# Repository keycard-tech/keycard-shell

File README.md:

# Keycard Shell

Keycard Shell transforms any Keycard into a standalone, air-gapped hardware wallet with built-in keypad, display, camera, and USB (which can be turned off). Fully open-source and EAL6+ certified, it uses ERC-4527 QR codes for secure signing and supports infinite removable backups.

## Main features

### Modular & Open Source

All firmware, hardware designs, and toolchain scripts are fully open source under the MIT license.

### Air-gapped Operation

Scan and display QR codes (ERC-4527) to sign transactions without ever exposing your keys.

### High-Security Secure Element

EAL6+ certified secure element for key storage and signing.

### Removable Smartcards

Support for an infinite number of Keycard smartcards, each with its own key & PIN.

### Wide Compatibility

Works seamlessly with MetaMask, imToken, Rabby, BlueWallet, Sparrow, Specter, and more.

### Built to Last

Powered by a replaceable Nokia BL-4C battery (25+ year expectancy), water & dust resistant.

### Duress PIN

A second PIN stops bad actors from stealing crypto by physical force

## About this repo

This repo contains everything needed to build a Keycard Shell.

### Repo structure

* `app`: the main firmware code. This is what makes everything happen.
* `bootloader`: the bootloader. Since it is non-upgradable we kept its complexity to a minimum.
* `cddl`: contains definitions for the various CBOR messages defined by the UR standard
* `deployment`: git-ignored folder containing the signing keys and build results
* `freertos`: we use FreeRTOS as our task scheduler.
* `hardware`: everything hardware related. From schematics up to case designs.
* `stm32`: all platform-specific code for the STM32H5 MCU. It also contains the project file for STM32CubeIDE needed to build the firmware.
* `test`: the tests firmware we run in the factory on each unit to check it has been properly assembled.
* `tools`: some tools used during the build process or during development.
* `zcbor`: the library we use to parse CBOR messages.

### Building the firmware

The Keycard Shell firmware build system uses CMake for the main firmware compilation and Python tools for post-processing (signing, image creation).

#### Getting the Code

First, clone the repository and switch to the release tag you want to build:

```bash
git clone https://github.com/keycard-tech/keycard-shell.git
cd keycard-shell
git checkout v1.1.1   # use the tag matching the official release you want to verify
```

make sure you follow the build instructions directly for the tag you checked out since some steps and toolchain versions can differ.

#### Prerequisites

##### Install Build Tools

**CMake** (3.15 or later) and **Ninja** are required for building the firmware.

On Ubuntu/Debian:
```bash
sudo apt install cmake ninja-build
```

On macOS (with Homebrew):
```bash
brew install cmake ninja
```

On Windows (with Chocolatey):
```bash
choco install cmake ninja
```

Alternatively, download from [cmake.org](https://cmake.org/download/) and [ninja-build.org](https://ninja-build.org/).

##### Install uv

```bash
curl -LsSf https://astral.sh/uv/install.sh | sh
```

or follow your OS instructions for installing uv.

##### Install ARM GCC Toolchain

Required for compiling STM32 firmware. The toolchain is automatically downloaded by the build script:

```bash
./tools/download-toolchain.sh
```

The script supports:
- Linux x86_64
- Linux aarch64
- macOS (Apple Silicon / arm64)
- Windows x86_64

After downloading, the toolchain is installed in `toolchain/`.

#### Setup Signing Keys

Create a `deployment` directory with two files:

- `bootloader-pubkey.txt`: Contains the public key the bootloader will use to verify the firmware. The key must be hex-encoded, uncompressed, and without the leading `04` byte.
- `fw-test-key.txt`: Contains a hex-encoded private key (the private part of the key in `bootloader-pubkey.txt`) used to sign the firmware.

#### Setup Virtual Environment

```bash
uv venv
uv sync
```

#### Build Firmware

```bash
cmake --preset release
cmake --build --preset release
```

#### Verifying the Firmware

After building, run:

```bash
uv run python tools/firmware-hash.py -b build/shellos.bin
```

Download the official binary from the [GitHub releases page](https://github.com/keycard-tech/keycard-shell/releases) and hash it the same way:

```bash
uv run python tools/firmware-hash.py -b ~/Downloads/shellos-<date>-<version>.bin
```

The two hashes must match.

#### Creating a Full Firmware Image

If you want to generate a full image to load on a device you built yourself, take a look at the `tools/create-image.py` script.

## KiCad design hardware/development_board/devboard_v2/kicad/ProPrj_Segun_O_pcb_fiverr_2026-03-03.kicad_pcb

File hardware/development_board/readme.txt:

For security reasons Shell in presales and sales have a locked bootloader that can only run firmwares which have been signed by Keycard CA key. This insures our users that they can trust the software they run. 

For developers who want to develop Shell firmware, you will find in this folder the full design of a development board for Shell

The folder '/devboard_v1' contains this design. Please note that there are some differences in the STM32 pinout between this development board version and shell board.

We'd need someone to update the layout of this dev board based on latest shell designs so that the dev board can actually run the shell builds.

Probably the best way to do this, would be to use the design and schematic from 'serial_run' version and make it in the form factor of this development board 

Get in touch with us either 
- on our discord server https://discord.gg/uJAXk7jFhZ
- our here with a GitHub issue or GitHub discussion

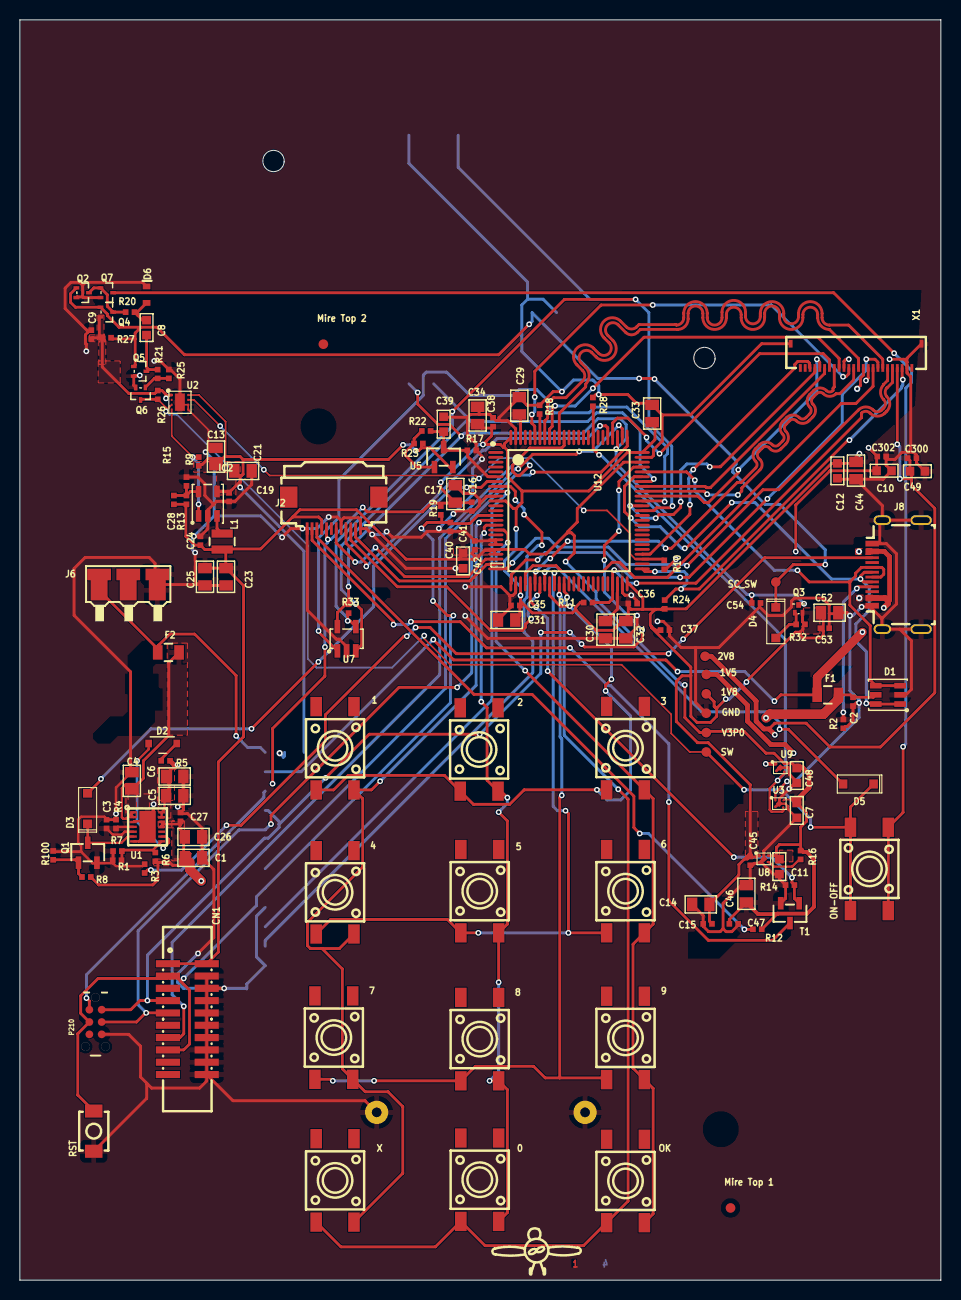
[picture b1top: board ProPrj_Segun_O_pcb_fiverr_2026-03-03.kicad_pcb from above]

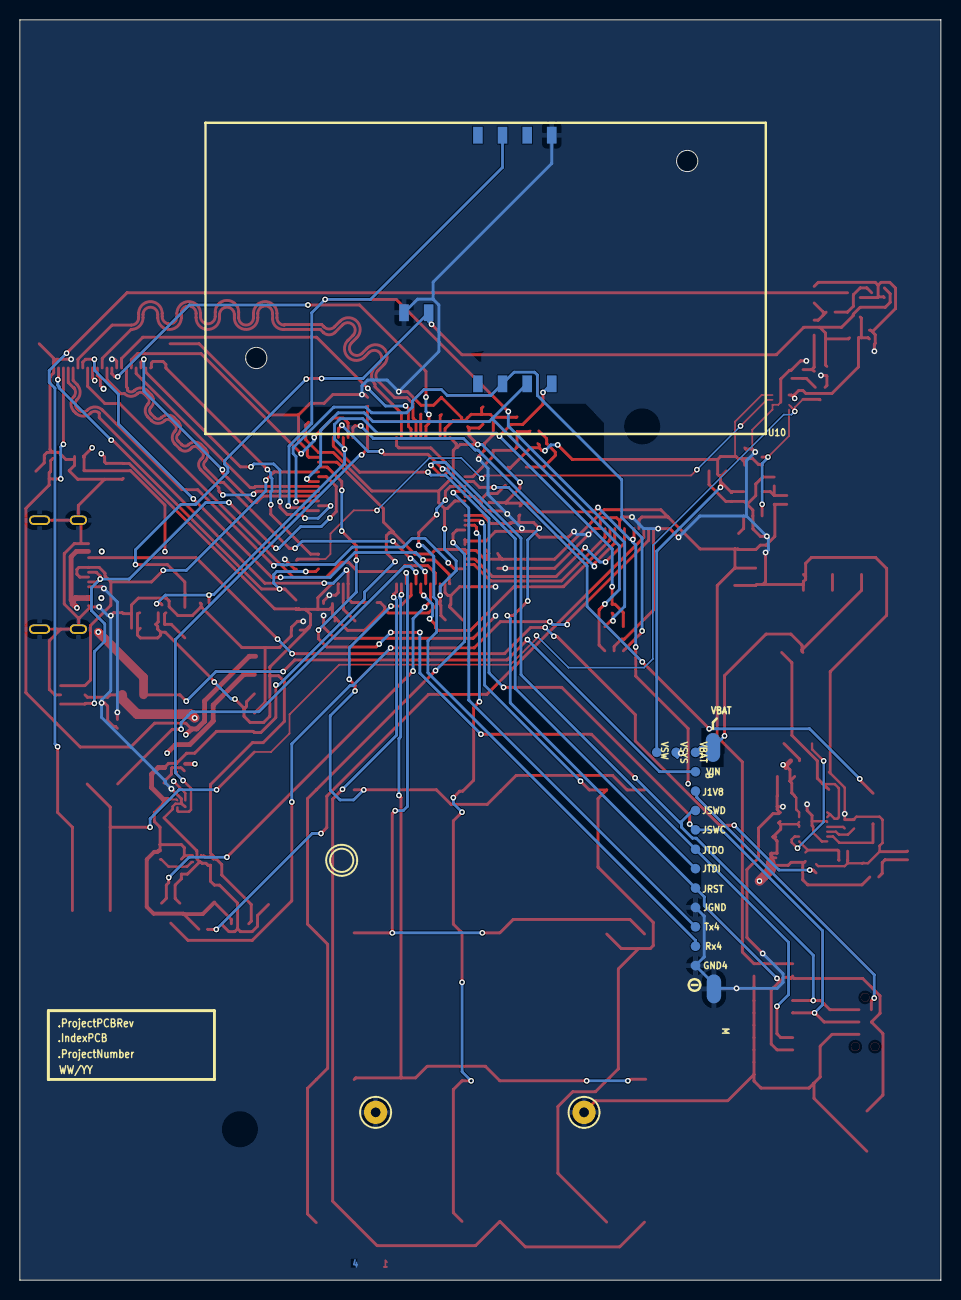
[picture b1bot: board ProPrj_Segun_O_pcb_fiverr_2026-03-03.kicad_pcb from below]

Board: 4 copper layers, 95.0 x 130.0 mm, 153 parts (17 on the bottom side), 85 nets.

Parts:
0, 1, 2, 3, 4, 5, 6, 7, 8, 9: KEY-SMD_4P-L6.0-W6.0-P3.90-LS9.0
1V5, 1V8, 2V8: TP; TESTPOINT_1MM
B: PLAGE_-_ROUGE
C1, C4, C5, C6, C13, C14, C17, C21, C23, C25, C26, C31, C32, C33, C34, C44, C46, C52: 4.7uF; 0805_-_CAPACITOR
C2, C9, C15, C16, C19, C24, C27, C35, C36, C37, C38, C40, C42, C45, C47, C53, C54, C300: 100nF; 0402_-_CAPACITOR
C3: 4.7uF; 0402_-_CAPACITOR
C7, C8, C10, C11, C12, C39, C41, C48: 1uF; 0603_-_CAPACITOR
C28: 9pF; 0402_-_CAPACITOR
C29, C30: 2.2uF; 0805_-_CAPACITOR
C49: 0603_-_CAPACITOR
C302: 0402_-_CAPACITOR
CN1: HX JN1.27-2x10 TP H4.9; CONN-SMD_HX-JN1.27-2X10-TP-H4.9
D1: 82400152; SOT23-6_0.95_VAR_AA
D2: LR_Y8SF-U1V2-1; OSRAM_LRY8SFU1V21
D3: MBR0530; SOD123_DIODE_INC
D4, D5: MBR0530T1G; SOD123_DIODE_INC
D6: BZX585-C3V0,115; SOD523_TOSHIBA
F1: BNP05000F000; 0805_-_FUSE
F2: 0ZCK0075FF2E; 0805_-_FUSE
GND: TESTPOINT_1MM
GND4: TP; TESTPOINT_1MM
IC2: SY8088IAAC; SOT23-5_0.95_VAR_AA
J1V8: TP; TESTPOINT_1MM
J2: FFC2B35-12-G; GCT_FFC2B35-12-G
J6: 1982633-1; TE_19826331
J8: U6252-35c; ANTENK_U6252-35C
JGND: TESTPOINT_1MM
JRST: TESTPOINT_1MM
JSWC: TESTPOINT_1MM
JSWD: TESTPOINT_1MM
JTDI: TESTPOINT_1MM
JTDO: TESTPOINT_1MM
L1: 2.2uH; CHILISON_BWF00252012
M: PLAGE_-_NOIRE
Mire Top 1, Mire Top 2: MIRE
OK: KEY-SMD_4P-L6.0-W6.0-P3.90-LS9.0
ON-OFF: KEY-SMD_4P-L6.0-W6.0-P3.90-LS9.0
P210: TC2030-MCP-NL
Q1: SOT23-VAR_AB
Q2: SOT-416-3
Q3: RZM002P02T2L; SOT-723
Q4, Q6, Q7: RE1C001ZPTL; SOT-416-3
Q5: RE1C001UNTCL; SOT-416-3
R1: ERTJ0EP473GM; 0402_-_RESISTOR
R2, R3, R4: 5.1kΩ; 0402_-_RESISTOR
R5: 200Ω; 0402_-_RESISTOR
R6: 40.2kΩ; 0402_-_RESISTOR
R7: 118kΩ; 0402_-_RESISTOR
R8, R11, R17, R18, R19, R20, R24: 10kΩ; 0402_-_RESISTOR
R9, R10, R14, R16, R28: 100kΩ; 0402_-_RESISTOR
R12: RC0402FR-0710RL; 0402_-_RESISTOR
R13: 205kΩ; 0402_-_RESISTOR
R15: 49.9kΩ; 0402_-_RESISTOR
R21, R22, R25, R32, R100: 220kΩ; 0402_-_RESISTOR
R23: 75kΩ; 0402_-_RESISTOR
R26: 750kΩ; 0402_-_RESISTOR
R27: 1MΩ; 0402_-_RESISTOR
R33: 11.5kΩ; 0402_-_RESISTOR
RST: SW-SMD_L4.0-W3.0-LS4.8
Rx4: TP; TESTPOINT_1MM
SC_SW: TESTPOINT_1MM
SW: TESTPOINT_1MM
T1: NTR3C21NZT1G; SOT23-VAR_AB
Tx4: TP; TESTPOINT_1MM
U1: MP2607DL-LF-P; QFN14-0.5-3S4
U2: XC6194AA05ER-G; TOREX_USP-8B06
U3: NCP115AMX150TCG; ON_SEMI_NCV8160AMX330TBG
U5: TLVH431AQDBZRG4; SOT23-VAR_AB
U7: ESDS312DBVR; SOT95P270X145-5N
U8: NCP115AMX180TCG; ON_SEMI_NCV8160AMX330TBG
U9: NCP115AMX280TCG; ON_SEMI_NCV8160AMX330TBG
U10: 5145300-3; SD-SMD_5145300-3
U12: STM32H573VIT6; LQFP-100_L14.0-W14.0-P0.50-LS16.0-BL
V3P0: TP; TESTPOINT_1MM
VBAT: TESTPOINT_1MM
VIN: TESTPOINT_1MM
VSW: TESTPOINT_1MM
VSYS: TESTPOINT_1MM
X: KEY-SMD_4P-L6.0-W6.0-P3.90-LS9.0
X1: HC-FPC-05-09-24RLTAG; HCTL_HC-FPC-05-09-24RLTAG

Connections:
$1N29: B.1, VBAT.1
$1N36: ON-OFF.3, ON-OFF.4
$1N37: ON-OFF.1, ON-OFF.2, SW.1
$2N6996: JRST.1, RST.2
/01POWER/BAT: C4.1, F2.2, U1.1 (BAT), U1.2 (BAT)
/01POWER/BAT_BSI: J6.2, J6.5
/01POWER/CC1: J8.A5 (CC1), R2.1
/01POWER/CC2: J8.B5 (CC2), R3.1, R3.2
/01POWER/USB_5V: F1.1, J8.A4_B9 (VBUS), J8.B4_A9 (VBUS)
/02MCU/MCU_BOOT0: R18.2, U12.94 (BOOT0)
/02MCU/VBAT: C39.2, R17.2, R22.1, U5.3 (A), U12.6 (VBAT)
/03PERIPHERALS/BL_A: J2.10, R12.1
/03PERIPHERALS/BL_K: J2.11, T1.3 (D)
CAM_D0: U12.68 (PA9), X1.19
CAM_D1: U12.64 (PC7), X1.21
CAM_D2: U12.54 (PB15), X1.22
CAM_D3: U12.66 (PC9), X1.20
CAM_D4: U12.79 (PC11), X1.18
CAM_D5: U12.92 (PB6), X1.16
CAM_D6: U12.95 (PB8), X1.14
CAM_D7: U12.90 (PB4), X1.12
CAM_HS: U12.29 (PA4), X1.9
CAM_I2C_SCL: R11.1, U12.47 (PB10)
CAM_I2C_SDA: R24.1, U12.51 (PB12)
CAM_PCLK: U12.31 (PA6), X1.17
CAM_PD: U12.26 (PA3), X1.8
CAM_RST: U12.25 (PA2), X1.6
CAM_VS: U12.93 (PB7), X1.7
CAM_XCLK: U12.67 (PA8), X1.13
GND: C1.2, C2.2, C3.2, C4.2, C5.2, C6.2, C7.1, C9.2, C10.1, C11.1, C12.1, C13.1, C14.1, C15.1, C16.1, C17.1, C19.2, C21.1, C23.1, C24.2, C25.1, C26.2, C27.2, C29.1, C30.1, C31.1, C32.1, C33.1, C34.1, C35.1, C36.1, C37.1, C38.1, C39.1, C40.2, C41.1, C42.1, C44.1, C45.1, C46.1, C47.1, C48.1, C49.2, C52.1, C53.1, C54.1, C300.1, C302.2, CN1.4, CN1.6, CN1.8, CN1.10, CN1.12, CN1.14, CN1.16, CN1.18, CN1.20, D1.2 (GND), GND.1, GND4.1 (PT), IC2.2 (GND), J2.1, J2.5, J2.12, J6.1, J6.4, J8.A1_B12 (GND), J8.B1_A12 (GND), J8.S1 (SHELL), J8.S2 (SHELL), J8.S3 (SHELL), J8.S4 (SHELL), JGND.1, M.1, P210.6, Q1.2, Q2.2, Q5.2 (S), Q6.2 (S), Q7.2 (S), R1.1, R2.2, R4.1, R7.1, R10.1, R14.1, R15.1, R17.1, R18.1, R25.1, R28.1, R100.1, RST.1, T1.2 (S), U1.3 (MODE), U1.7 (GND), U1.TH_PAD (GND), U2.5 (GND), U2.6 (TEST), U2.TH_PAD, U3.2 (GND), U3.5 (EP), U7.2 (GND), U8.2 (GND), U8.5 (EP), U9.2 (GND), U9.5 (EP), U10.C5, U10.C10, U12.10 (VSS), U12.19 (VSSA), U12.20 (VREF-), U12.27 (VSS), U12.49 (VSS), U12.74 (VSS), U12.99 (VSS), X1.0, X1.2, X1.15
JTCK_SWCLK: CN1.9, JSWC.1, P210.4, U12.76 (PA14)
JTDI: JTDI.1, U12.77 (PA15)
JTDO_SWO: CN1.13, JTDO.1, U12.89 (PB3)
JTMS_SWDIO: CN1.7, JSWD.1, P210.2, U12.72 (PA13)
KBD_C0: 3.2, 6.2, 9.2, OK.2, U12.17 (PC2)
KBD_C1: 0.2, 2.2, 5.2, 8.2, U12.16 (PC1)
KBD_C2: 1.2, 4.2, 7.2, U12.15 (PC0), X.2
KBD_R0: 0.4, OK.4, U12.37 (PB2), X.4
KBD_R1: 7.4, 8.4, 9.4, U12.36 (PB1)
KBD_R2: 4.4, 5.4, 6.4, U12.35 (PB0)
KBD_R3: 1.4, 2.4, 3.4, U12.34 (PC5)
MCU_RST: CN1.3, CN1.15, P210.3
MCU_SC_PRES: C54.2, Q3.3 (D), R33.2, U7.5 (I/O2), U12.78 (PC10)
MCU_USB2_N: D1.1 (I/O1), D1.6 (I/O1), J8.A7 (DN1), J8.B7 (DN2), U12.70 (PA11)
MCU_USB2_P: D1.3 (I/O2), D1.4 (I/O2), J8.A6 (DP1), J8.B6 (DP2), U12.71 (PA12)
unnamed: F2.1, J6.3, J6.6
unnamed: C29.2, U12.98 (VCAP)
unnamed: C30.2, U12.48 (VCAP)
unnamed: D2.1 (C), U1.9 (~STAT2~)
unnamed: Q3.1 (G), R32.1
unnamed: Q6.3 (D), R26.1, U2.3 (SW)
unnamed: C8.2, R20.2
unnamed: C28.1, IC2.5 (FB), R13.1, R15.2
unnamed: IC2.3 (L), L1.1
unnamed: Q4.2 (S), Q7.1 (G), R20.1
unnamed: C8.1, Q5.3 (D), R21.1
unnamed: Q6.1 (G), R21.2, R25.2
unnamed: R8.1, R100.2
unnamed: Rx4.1 (PT), U12.8 (PC14-OSC32_IN)
unnamed: Tx4.1 (PT), U12.9 (PC15-OSC32_OUT)
unnamed: R4.2, U1.4 (ICHSET)
unnamed: R1.2, R6.1, R7.2, U1.8 (NTC)
unnamed: C3.1, U1.5 (TMR)
unnamed: R22.2, R23.1, U5.1 (REF)
unnamed: R16.1, U8.3 (EN)
unnamed: C40.1, R19.2, U12.14 (NRST)
PWR_CAM_EN: R28.2, U9.3 (EN), U12.83 (PD2)
PWR_KILL: R10.2, U2.7 (SHDN), U12.53 (PB14)
SCR_BL_PWM: R14.2, T1.1 (G), U12.30 (PA5)
SCR_D/C: J2.6, U12.23 (PA0)
SCR_RST: J2.2, U12.24 (PA1)
SCR_SPI_MOSI: J2.3, U12.32 (PA7)
SCR_SPI_SCK: J2.4, U12.80 (PC12)
SC_PRES_SW: Q2.1, Q4.1 (G), Q5.1 (G), R27.1, SC_SW.1, U10.C9
SC_RST: U7.3 (NC), U12.69 (PA10)
SC_USART_CLK: U7.1 (NC), U12.65 (PC8)
SC_USART_TX: R33.1, U7.4 (I/O1), U12.63 (PC6)
SYS_PG: IC2.1 (EN), R9.1, U2.4 (PG)
V1P5: 1V5.1 (PT), C10.2, C302.1, U3.1 (OUT), X1.10
V1P8: 1V8.1 (PT), C12.2, C14.2, C15.2, C16.2, C17.2, C31.2, C32.2, C33.2, C34.2, C35.2, C36.2, C37.2, C38.2, C44.2, C45.2, C52.2, C53.2, J1V8.1 (PT), J2.8, P210.1, Q3.2 (S), R11.2, R19.1, R24.2, R32.2, U8.1 (OUT), U12.11 (VDD), U12.28 (VDD), U12.50 (VDD), U12.75 (VDD), U12.100 (VDD), X1.11
V2P8: 2V8.1 (PT), C49.1, C300.2, U9.1 (OUT), X1.4
V3P0: C7.2, C11.2, C23.2, C24.1, C25.2, C28.2, C41.2, C42.2, C46.2, C47.2, C48.2, CN1.1, CN1.2, J2.9, L1.2, R12.2, R13.2, R16.2, U3.4 (IN), U8.4 (IN), U9.4 (IN), U12.21 (VREF+), U12.22 (VDDA), U12.73 (VDDUSB), V3P0.1 (PT)
VSYS: C5.1, C6.1, C9.1, Q4.3 (D), R5.1, R5.2, R26.2, R27.2, U1.13 (SYS), U1.14 (SYS), U2.1 (VIN), VSYS.1
VSYS_SWITCHED: C13.2, C19.1, C21.2, IC2.4 (VIN), R9.2, R23.2, U2.8 (VOUT), U5.2 (C), VSW.1
VUSB: C1.1, C2.1, C26.1, C27.1, D1.5 (VBUS), F1.2, R6.2, R8.2, U1.11 (IN), U1.12 (IN)

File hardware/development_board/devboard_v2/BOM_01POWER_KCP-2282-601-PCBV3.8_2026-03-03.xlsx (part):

No. | Quantity | Designator | Footprint | Value | Manufacturer Part | Manufacturer | Supplier Part | Supplier | Name | Unique ID | Device | LCSC Part Name | Datasheet | LCSC Stock | LCSC Price | Pin Count | Primary Category | Secondary Category | Comment | JLCPCB Stock | JLCPCB Price | Layer
1 | 21 | 1V5,1V8,2V8,GND,GND4,J1V8,JGND,JRST,JSWC,JSWD,JTDI,JTDO,Rx4,SC_SW,SW,Tx4,V3P0,V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 | TESTPOINT 1MM |  |  |  |  |  | TP | 4a4fe6a51a1cc0a2,6c9f92e61b7c87b6,7cdf3eb797e9b109,65b9dc4ad4388d00,73e673facf0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 | TP |  |  |  | 0.0349 | 1 |  |  | TP |  |  | T
2 | 1 | B | PLAGE - ROUGE |  |  |  |  |  | TP | fe57bcca61014095 | TP |  |  |  | 0.0349 | 1 |  |  | TP |  |  | T
3 | 18 | C1,C4,C5,C6,C13,C14,C17,C21,C23,C25,C26,C31,C32,C33,C34,C44,C46,C52 | C0805 | 4.7uF | 0805X475M250NT | FH(风华) | C2857998 | LCSC | 4.7uF |  | 0805X475M250NT | 4.7uF ±20% 25V | https://item.szlcsc.com/datasheet/0805X475M250NT/3058809.html |  |  | 2 | Capacitors | Multilayer Ceramic Capacitors MLCC - SMD/SMT | 4.7uF | 36 | 0.0024 | B
4 | 19 | C2,C9,C15,C16,C19,C24,C27,C35,C36,C37,C38,C40,C42,C45,C47,C53,C54,C300,C302 | C0402 | 100nF | 0402B104K500CT | Walsin(华新科) | C152814 | LCSC | 100nF |  | 0402B104K500CT | 100nF ±10% 50V | https://item.szlcsc.com/datasheet/0402B104K500CT/164155.html |  |  | 2 | Capacitors | Multilayer Ceramic Capacitors MLCC - SMD/SMT | 100nF | 3506320 | 0.0004 | T
5 | 1 | C3 | C0402 | 4.7uF | CC0402KRX5R6BB475 | YAGEO(国巨) | C326586 | LCSC | 4.7uF |  | CC0402KRX5R6BB475 | 4.7uF ±10% 10V | https://item.szlcsc.com/datasheet/CC0402KRX5R6BB475/306680.html |  |  | 2 | Capacitors | Multilayer Ceramic Capacitors MLCC - SMD/SMT | 4.7uF | 207401 | 0.0027 | T
6 | 9 | C7,C8,C10,C11,C12,C39,C41,C48,C49 | C0603 | 1uF | 0603X105K500CT | Walsin(华新科) | C141872 | LCSC | 1uF |  | 0603X105K500CT | 1uF ±10% 50V | https://atta.szlcsc.com/upload/public/pdf/source/20181012/C1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 |  |  | 2 | Capacitors | Multilayer Ceramic Capacitors MLCC - SMD/SMT | 1uF | 12805 | 0.0015 | T
7 | 1 | C28 | C0402 | 9pF | GJM1555C1H9R0CB01D | muRata(村田) | C85884 | LCSC | 9pF |  | GJM1555C1H9R0CB01D | ±0.25pF 9pF 50V | https://item.szlcsc.com/datasheet/GJM1555C1H9R0CB01D/87060.html |  |  | 2 | Capacitors | Multilayer Ceramic Capacitors MLCC - SMD/SMT | 9pF | 30460 | 0.0024 | T
8 | 2 | C29,C30 | C0805 | 2.2uF | CL21B225KAFNNNE | SAMSUNG(三星) | C19110 | LCSC | 2.2uF |  | CL21B225KAFNNNE | 2.2uF ±10% 25V | https://item.szlcsc.com/datasheet/CL21B225KAFNNNE/19814.html |  |  | 2 | Capacitors | Multilayer Ceramic Capacitors MLCC - SMD/SMT | 2.2uF | 795858 | 0.0023 | T
9 | 1 | CN1 | CONN-SMD_HX-JN1.27-2X10-TP-H4.9 |  | HX JN1.27-2x10 TP H4.9 | hanxia(韩下) | C42455947 | LCSC | HX JN1.27-2x10 TP H4.9 | gge18 | HX JN1.27-2x10 TP H4.9 | 1.27mm 2x10P 排数:2 每排P数:10 | https://item.szlcsc.com/datasheet/HX%2520JN1.27-2x10%2520TP%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 |  |  | 20 | Connectors | IDC Connectors | HX JN1.27-2x10 TP H4.9 | 349 | 0.0563 | T
10 | 1 | D1 | SOT-563_L1.6-W1.2-P0.50-LS1.6-BL |  | 82400152 | TECH PUBLIC(台舟) | C22435121 | LCSC | 82400152 |  | 82400152_C22435121 | 低电容TVS二极管阵列 | https://item.szlcsc.com/datasheet/82400152/24062289.html |  |  | 6 | Circuit Protection | ESD and Surge Protection (TVS/ESD) | 82400152 | 4005 | 0.0106 | T
11 | 1 | D2 | OSRAM LRY8SFU1V21 |  | LR Y8SF-U1V2-1-0-20-R18-Z | OSRAM | C2899969 | LCSC | LR_Y8SF-U1V2-1 | cca08e5caf06c018 | LR_Y8SF-U1V2-1 |  |  |  | 0.0349 | 2 |  |  | LR_Y8SF-U1V2-1 |  |  | T
12 | 1 | D3 | SOD-123_L2.7-W1.6-LS3.7-RD-1 |  | MBR0530 | YANGJIE(扬杰) | C699108 | LCSC | MBR0530 |  | MBR0530_C699108 | 电压:30V 电流:500mA | https://item.szlcsc.com/datasheet/MBR0530/733800.html |  |  | 2 | Diodes | Schottky Diodes | MBR0530 | 4211 | 0.0066 | T
13 | 2 | D4,D5 | SOD-123_L2.7-W1.6-LS3.7-RD-1 |  | MBR0530T1G | onsemi(安森美) | C82046 | LCSC | MBR0530T1G |  | MBR0530T1G | 电压:30V 电流:500mA | https://item.szlcsc.com/datasheet/MBR0530T1G/83201.html |  |  | 2 | Diodes | Schottky Diodes | MBR0530T1G | 19589 | 0.0105 | B
14 | 1 | D6 | SOD-523_L1.2-W0.8-LS1.6-RD |  | BZX585-C3V0,115 | Nexperia(安世) | C550648 | LCSC | BZX585-C3V0,115 |  | BZX585-C3V0,115 | 稳压二极管 | https://item.szlcsc.com/datasheet/BZX585-C3V0%252C115/571729.html |  |  | 2 | Diodes | Zener Diodes | BZX585-C3V0,115 | 1167 | 0.0194 | T
15 | 1 | F1 | 0805 - FUSE |  | 0805L050WR | Littelfuse | C207022 | LCSC | 0ZCK0075FF2E | 09f31a4987c8a883,dce76cdd9f7f4243 | 0ZCK0075FF2E |  |  |  | 0.0349 | 2 |  |  | 0ZCK0075FF2E,BNP05000F000 |  |  | T
 | 1 | F2 | 0805 - FUSE |  | 0805L050WR | Littelfuse | C207022 | LCSC | BNP05000F000 |  | BNP05000F000 |  |  |  |  |  |  |  |  |  |  | T
17 | 1 | IC2 | SOT23-5 0.95 VAR AA |  | SY8088IAAC | Silergy | C479072 | LCSC | SY8088IAAC | 9c081cc57a023191 | SY8088IAAC |  |  |  | 0.0349 | 5 |  |  | SY8088IAAC |  |  | T
18 | 1 | J2 | GCT FFC2B35-12-G |  | FPC-05F-12PH20 | XUNPU | C2856799 | LCSC | FFC2B35-12-G | 1fb9863844ab5169 | FFC2B35-12-G |  |  |  | 0.0349 | 12 |  |  | FFC2B35-12-G |  |  | B
19 | 1 | J6 | TE 19826331 |  | 1982633-1 | TE Connectivity | C5877665 | LCSC | 1982633-1 | be1703a8306ee88a | 1982633-1 |  |  |  | 0.0349 | 6 |  |  | 1982633-1 |  |  | T
20 | 1 | J8 | ANTENK U6252-35C |  | TYPE-C 16P CB1.6 073 | SHOU HAN | C2906290 | LCSC | U6252-35c | 5c2e899d33916bcd | U6252-35c |  |  |  | 0.0349 | 16 |  |  | U6252-35c |  |  | T
21 | 1 | L1 | IND-SMD_L2.5-W2.0-1 | 2.2uH | BWVF002520122R2M00 | Chilisin(奇力新) | C2838263 | LCSC | 2.2uH |  | BWVF002520122R2M00 | 2.2uH ±20% 1.8A | https://item.szlcsc.com/datasheet/BWVF002520122R2M00/3012588.html |  |  | 2 | Inductors, Coils, Chokes | Power Inductors | 2.2uH | 60 | 0.0073 | T
22 | 1 | M | PLAGE - NOIRE |  |  |  |  |  | TP | dcc3ce6d5d8a1361 | TP |  |  |  | 0.0349 | 1 |  |  | TP |  |  | T
23 | 2 | Mire Top 1,Mire Top 2 | MIRE |  |  |  |  |  | DNI | 6dfc160cef736230,c06f29e3df15be78 | DNI |  |  |  | 0.0349 | 0 |  |  | DNI |  |  | T
24 | 1 | P210 | TC2030-MCP-NL |  |  |  |  |  | TC2030-MCP-NL | 252b89c920cef1b9 | TC2030-MCP-NL |  |  |  | 0.0349 | 6 |  |  | TC2030-MCP-NL |  |  | T
25 | 1 | Q3 | SOT-723_L1.2-W0.8-P0.40-LS1.2-BR |  | RZM002P02T2L | ROHM(罗姆) | C253531 | LCSC | RZM002P02T2L |  | RZM002P02T2L | 1个P沟道 耐压:20V 电流:200mA | https://item.szlcsc.com/datasheet/RZM002P02T2L/248221.html |  |  | 3 | Transistors/Thyristors | MOSFETs | RZM002P02T2L | 6857 | 0.0086 | T
26 | 1 | Q4 | SC-89-3_L1.6-W0.9-P1.00-LS1.6-BR |  | RE1C001ZPTL | ROHM(罗姆) | C703629 | LCSC | RE1C001ZPTL |  | RE1C001ZPTL | 1个P沟道 耐压:20V 电流:100mA | https://item.szlcsc.com/datasheet/RE1C001ZPTL/739440.html |  |  | 3 | Transistors/Thyristors | MOSFETs | RE1C001ZPTL | 4229 | 0.0074 | T
27 | 4 | Q2,Q5,Q6,Q7 | SC-89-3_L1.6-W0.9-P1.00-LS1.6-BR |  | RE1C001UNTCL | ROHM(罗姆) | C253519 | LCSC | RE1C001UNTCL |  | RE1C001UNTCL | 1个N沟道 耐压:20V 电流:100mA | https://item.szlcsc.com/datasheet/RE1C001UNTCL/248209.html |  |  | 3 | Transistors/Thyristors | MOSFETs | RE1C001UNTCL | 4358 | 0.0056 | T
28 | 1 | Q1 | SOT-23-3_L2.9-W1.3-P0.95-LS2.4-BR |  | BSS123-TP | MCC(美微科) | C6521970 | LCSC | BSS123-TP |  | BSS123-TP | 1个N沟道 耐压:100V | https://item.szlcsc.com/datasheet/BSS123-TP/7475168.html |  |  | 3 | Transistors/Thyristors | MOSFETs | BSS123-TP | 97 | 0.0045 | T
29 | 1 | R1 | R0402 |  | ERTJ0EP473GM | PANASONIC(松下) | C336818 | LCSC | ERTJ0EP473GM |  | ERTJ0EP473GM | 47kΩ 电阻精度:±2% 4050K | https://atta.szlcsc.com/upload/public/pdf/source/20200515/C3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 |  |  | 2 | Sensors | NTC Thermistors | ERTJ0EP473GM | 0 | 0.0209 | T
30 | 3 | R2,R3,R4 | R0402 | 5.1kΩ | RC0402FR-075K1L | YAGEO(国巨) | C105872 | LCSC | 5.1kΩ |  | RC0402FR-075K1L | 厚膜电阻 5.1kΩ ±1% 62.5mW | https://item.szlcsc.com/datasheet/RC0402FR-075K1L/107087.html |  |  | 2 | Resistors | Chip Resistor - Surface Mount | 5.1kΩ | 1186629 | 0.0002 | B
31 | 1 | R5 | R0402 | 200Ω | RC0402FR-07200RL | YAGEO(国巨) | C114764 | LCSC | 200Ω |  | RC0402FR-07200RL | 厚膜电阻 200Ω ±1% 62.5mW | https://item.szlcsc.com/datasheet/RC0402FR-07200RL/116008.html |  |  | 2 | Resistors | Chip Resistor - Surface Mount | 200Ω | 482200 | 0.0002 | T
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
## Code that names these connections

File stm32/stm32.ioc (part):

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Mcu.Name=STM32H573VITx
Mcu.Package=LQFP100
Mcu.UserName=STM32H573VITx
PA0.GPIOParameters=GPIO_Label
PA0.GPIO_Label=GPIO_LCD_CD
PA0.Signal=GPIO_Output
PA1.GPIOParameters=PinState,GPIO_Label
PA1.GPIO_Label=GPIO_LCD_RST
PA1.PinState=GPIO_PIN_SET
PA1.Signal=GPIO_Output
PA10.GPIOParameters=GPIO_Label
PA10.GPIO_Label=GPIO_CARD_RST
PA10.Signal=GPIO_Output
PA11.Mode=Device
PA11.Signal=USB_DM
PA12.Mode=Device
PA12.Signal=USB_DP
PA13(JTMS/SWDIO).GPIOParameters=GPIO_Label
PA13(JTMS/SWDIO).GPIO_Label=SWDIO
PA13(JTMS/SWDIO).Mode=Trace_Asynchronous_SW
PA13(JTMS/SWDIO).Signal=DEBUG_JTMS-SWDIO
PA14(JTCK/SWCLK).GPIOParameters=GPIO_Label
PA14(JTCK/SWCLK).GPIO_Label=SWCLK
PA14(JTCK/SWCLK).Mode=Trace_Asynchronous_SW
PA14(JTCK/SWCLK).Signal=DEBUG_JTCK-SWCLK
PA2.GPIOParameters=PinState,GPIO_Label
PA2.GPIO_Label=GPIO_CAMERA_RST
PA2.PinState=GPIO_PIN_SET
PA2.Signal=GPIO_Output
PA3.GPIOParameters=GPIO_Label
PA3.GPIO_Label=GPIO_CAMERA_PWDN
PA3.Signal=GPIO_Output
PA4.Mode=Slave_8_bits_External_Synchro
PA4.Signal=DCMI_HSYNC
PA5.GPIOParameters=GPIO_Label
PA5.GPIO_Label=PWM_LCD_BL
PA5.Signal=S_TIM2_CH1
PA6.Mode=Slave_8_bits_External_Synchro
PA6.Signal=DCMI_PIXCLK
PA7.GPIOParameters=GPIO_Speed
PA7.GPIO_Speed=GPIO_SPEED_FREQ_HIGH
PA7.Mode=TX_Only_Simplex_Unidirect_Master
PA7.Signal=SPI6_MOSI
PA8.GPIOParameters=GPIO_Label
PA8.GPIO_Label=CAM_XCLK
PA8.Mode=Clock-out
PA8.Signal=RCC_MCO_1
PA9.Mode=Slave_8_bits_External_Synchro
PA9.Signal=DCMI_D0
PB0.GPIOParameters=PinState,GPIO_PuPd,GPIO_Label,GPIO_ModeDefaultOutputPP
PB0.GPIO_Label=GPIO_KEYPAD_ROW_1
PB0.GPIO_ModeDefaultOutputPP=GPIO_MODE_OUTPUT_OD
PB0.GPIO_PuPd=GPIO_NOPULL
PB0.PinState=GPIO_PIN_SET
PB0.Signal=GPIO_Output
PB1.GPIOParameters=PinState,GPIO_PuPd,GPIO_Label,GPIO_ModeDefaultOutputPP
PB1.GPIO_Label=GPIO_KEYPAD_ROW_2
PB1.GPIO_ModeDefaultOutputPP=GPIO_MODE_OUTPUT_OD
PB1.GPIO_PuPd=GPIO_NOPULL
PB1.PinState=GPIO_PIN_SET
PB1.Signal=GPIO_Output
PB10.Mode=I2C
PB10.Signal=I2C2_SCL
PB12.Mode=I2C
PB12.Signal=I2C2_SDA
PB14.GPIOParameters=GPIO_Label
PB14.GPIO_Label=GPIO_PWR_KILL
PB14.Signal=GPIO_Output
PB15.Mode=Slave_8_bits_External_Synchro
PB15.Signal=DCMI_D2
PB2.GPIOParameters=PinState,GPIO_PuPd,GPIO_Label,GPIO_ModeDefaultOutputPP
PB2.GPIO_Label=GPIO_KEYPAD_ROW_3
PB2.GPIO_ModeDefaultOutputPP=GPIO_MODE_OUTPUT_OD
PB2.GPIO_PuPd=GPIO_NOPULL
PB2.PinState=GPIO_PIN_SET
PB2.Signal=GPIO_Output
PB3(JTDO/TRACESWO).GPIOParameters=GPIO_Label
PB3(JTDO/TRACESWO).GPIO_Label=SWO
PB3(JTDO/TRACESWO).Mode=Trace_Asynchronous_SW
PB3(JTDO/TRACESWO).Signal=DEBUG_JTDO-SWO
PB4(NJTRST).Mode=Slave_8_bits_External_Synchro
PB4(NJTRST).Signal=DCMI_D7
PB6.Mode=Slave_8_bits_External_Synchro
PB6.Signal=DCMI_D5
PB7.Mode=Slave_8_bits_External_Synchro
PB7.Signal=DCMI_VSYNC
PB8.Mode=Slave_8_bits_External_Synchro
PB8.Signal=DCMI_D6
PC0.GPIOParameters=GPIO_PuPd,GPIO_Label
PC0.GPIO_Label=GPIO_KEYPAD_COL_2
PC0.GPIO_PuPd=GPIO_PULLUP
PC0.Signal=GPIO_Input
PC1.GPIOParameters=GPIO_PuPd,GPIO_Label
PC1.GPIO_Label=GPIO_KEYPAD_COL_1
PC1.GPIO_PuPd=GPIO_PULLUP
PC1.Signal=GPIO_Input
PC10.GPIOParameters=GPIO_PuPd,GPIO_Label,GPIO_ModeDefaultEXTI
PC10.GPIO_Label=GPIO_SC_PRES
PC10.GPIO_ModeDefaultEXTI=GPIO_MODE_IT_RISING_FALLING
PC10.GPIO_PuPd=GPIO_PULLDOWN
PC10.Signal=GPXTI10
PC11.Mode=Slave_8_bits_External_Synchro
PC11.Signal=DCMI_D4
PC12.GPIOParameters=GPIO_Speed,GPIO_PuPd
PC12.GPIO_PuPd=GPIO_PULLUP
PC12.GPIO_Speed=GPIO_SPEED_FREQ_HIGH
PC12.Mode=TX_Only_Simplex_Unidirect_Master
PC12.Signal=SPI6_SCK
PC13.GPIOParameters=GPIO_PuPd,GPIO_Label,GPIO_ModeDefaultEXTI
PC13.GPIO_Label=GPIO_VUSB_OK
PC13.GPIO_ModeDefaultEXTI=GPIO_MODE_IT_RISING_FALLING
PC13.GPIO_PuPd=GPIO_PULLUP
PC13.Signal=GPXTI13
PC2.GPIOParameters=GPIO_PuPd,GPIO_Label
PC2.GPIO_Label=GPIO_KEYPAD_COL_0
PC2.GPIO_PuPd=GPIO_PULLUP
PC2.Signal=GPIO_Input
PC4.GPIOParameters=GPIO_PuPd,GPIO_Label,GPIO_ModeDefaultEXTI
PC4.GPIO_Label=GPIO_HALT_REQ
PC4.GPIO_ModeDefaultEXTI=GPIO_MODE_IT_RISING_FALLING
PC4.GPIO_PuPd=GPIO_PULLUP
PC4.Signal=GPXTI4
PC5.GPIOParameters=PinState,GPIO_PuPd,GPIO_Label,GPIO_ModeDefaultOutputPP
PC5.GPIO_Label=GPIO_KEYPAD_ROW_0
PC5.GPIO_ModeDefaultOutputPP=GPIO_MODE_OUTPUT_OD
PC5.GPIO_PuPd=GPIO_NOPULL
PC5.PinState=GPIO_PIN_SET
PC5.Signal=GPIO_Output
PC6.Mode=SmartCard_With_Clock
PC6.Signal=USART6_TX
PC7.Mode=Slave_8_bits_External_Synchro
PC7.Signal=DCMI_D1
PC8.Mode=SmartCard_With_Clock
PC8.Signal=USART6_CK
PC9.Mode=Slave_8_bits_External_Synchro
PC9.Signal=DCMI_D3
PD2.GPIOParameters=GPIO_Label
PD2.GPIO_Label=GPIO_CAM_EN
PD2.Signal=GPIO_Output
RCC.HSE_VALUE=8000000
RCC.SYSCLKFreq_VALUE=250000000
RCC.SYSCLKSource=RCC_SYSCLKSOURCE_PLLCLK
board=custom

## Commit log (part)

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2025-07-14 remove some unused files
2025-07-14 make simple reproducible database builds
2025-07-15 update abi list format
2025-07-15 update docs
2025-07-24 start slip39 implementation
2025-07-25 continue shamir secret sharing implementation
2025-07-29 complete implemention of SLIP39 (API wip)
2025-07-30 start slip39 refactoring
2025-07-30 fix rs1024 checksum verification
2025-07-31 simpler slip39_generate
2025-08-01 rewrite shard and group combination functions
2025-08-01 make wordlist for autocompletion configurable
2025-08-01 add support for displaying slip39 mnemonics
2025-08-01 increment HDPL upon exiting bootloader
2025-08-04 fixed typo
2025-08-04 remove decryption from slip39_combine
2025-08-04 initial slip39 ui work
2025-08-04 grow stack for core task
2025-08-05 add connection params
2025-08-05 implement slip39 generation
2025-08-05 add slip39 prompt
2025-08-05 add correct message
2025-08-05 more ui improvements
2025-08-06 refactor keycard initialization code
2025-08-06 add part left counter for slip39
2025-08-06 avoid shadowing variable
2025-08-06 prepare release
2025-08-06 change old applet message
2025-08-07 add prototype keycard-based signing
2025-08-11 use VUSB_OK to determine charging status
2025-08-11 handle btc tx with marker/flag
2025-08-11 add elabel
2025-08-11 proper change output detection
2025-08-19 default to chainID 1 for legacy tx
2025-08-19 improve public key export via USB
2025-08-19 change PID
2025-08-19 move chainid initialization
2025-08-19 remove useless memory optimization
2025-08-19 fix some usb-related functions
2025-08-19 remove further premature optimizations
2025-08-20 fix accessing parameters after CANCEL state
2025-08-20 always use output var
2025-08-20 add mcu status test
2025-08-20 adjust path
2025-08-21 add connection parameters
2025-08-22 remove outdated port
2025-08-25 update keycard-py
2025-08-26 only import tkinter when needed
2025-08-28 fix odd length hex string hashing
2025-08-29 remove outdated code
2025-09-17 add skip help settings
2025-09-17 restructure some menus
2025-09-17 add more inline instructions
2025-09-18 further restructure menus
2025-09-23 start usb protocol documentation
2025-09-24 remove unnecessary check
2025-09-24 document all USB commands
2025-09-29 remove title in QR output to increase QR size
2025-10-06 fixed displaying QR UR with title
2025-10-06 remove title from dev verification QR
2025-10-09 add device csv script
2025-10-14 change db and web keys
2025-10-16 fix verify URL
2025-10-23 filter non-eth chains/tokens
2025-10-24 Update link for source JSON files in shell-db.md (#179)
2025-10-28 make verifyingContract and chainId optional in EIP712Domain
2025-11-10 add eip712 hash to all eip712 messages
2025-11-10 prepare for release
2025-11-17 initial decoding
2025-11-26 add keycard signing option for database
2025-11-27 finalize execute internal decoding
2025-11-27 Execute decoding (#188)
    decode individual function calls inside universal router's execute function
2025-11-28 remove taproot key from key export
2025-12-02 fix psbt out writing
2025-12-29 support #6.310 tagged psbt
2026-01-16 update script
2026-01-16 misc fixes
2026-01-19 explicit MPU configuration
2026-01-20 more robust t1 rx
2026-01-28 Add serial run hardware and mechanical files, remove spaces from filenames
    - Added new serial_run directory with hardware documentation
    - Renamed files in pilot_run and prototype_P2 to remove spaces
    - Updated electronics, mechanical parts, and BOM files
2026-01-29 Add KCP-2282 schematic V3.8 and updated assembly STEP file
2026-01-29 Improve hardware README guidance
2026-01-29 Revise readme for Keycard Shell and deprecation notice
    Updated the readme to reflect the deprecation of pilot_run and prototype_v2 versions, and improved section formatting.
2026-01-30 better verification instructions
2026-02-02 Update readme with layout update instructions
    Added instructions for updating the development board layout.
2026-02-03 add multiple path export
2026-02-03 add beta + downgrade protection
2026-02-04 fix alternative account gen
2026-02-05 add extra symbol keyboard (navigation tbd)
2026-02-05 implement extra navigation
2026-02-05 simplify num keyboard navigation
2026-02-09 fix typo
2026-02-09 fix sha3_256 even if function is unused.
2026-02-09 fix another typo
2026-02-09 always use memzero for cleanup
2026-02-09 add bound check for PSBT_IN_WITNESS_UTXO
2026-02-09 add bound checks for PSBT BIP32 IN/OUT
2026-02-09 validate card signature length
2026-02-09 add sanity check on get data reply from card
2026-02-09 check result from ecdsa_get_public_key65
2026-02-09 sanity check to usb command header for PSBT
2026-02-09 check first segment header length in db upgrade usb command
2026-02-09 add check to bip32 length when getting parent fingerprint
2026-02-09 check bip32 path len to be multiple of 4
2026-02-09 add PSBT_IN_SIGHASH_TYPE length check
2026-02-09 add lr length check
2026-02-09 validate pair response length
2026-02-09 check that uint256 length is not exceeded in input json
2026-02-09 enforce null terminator for card name
2026-02-09 check for malformed pps
2026-02-09 rename aes_cmac to aes_cbc_mac
2026-02-09 remove undefined CONFIDENTIAL memory section and move allocations to stack
2026-02-09 cleanup stack on hal_rng_next return
2026-02-09 prepare for next beta
2026-02-09 PSBT header must be at least 5 bytes long
2026-02-09 add bound check for last byte
2026-02-09 add missing parentheses for consistency
2026-02-09 add usage comment to `eip712_to_string`
2026-02-09 add usage comment for `core_eth_process_eip712`
2026-02-10 fixed length encoding when script_len > 253 for legacy inputs
2026-02-10 limit tag and length parsing to uint16_t size
2026-02-10 improve t1 error handling
2026-02-10 fix read/set card name
2026-02-16 add backslash to symbol keyboard
2026-02-18 increase bip39 passphrase max len and make input field scroll
2026-02-20 add check for malformed card responses
2026-02-27 add missing newline
2026-03-06 fix regression in setting card name
2026-03-10 show fingerprint when no card name set
2026-03-10 add quick brightness settings to qrout
2026-03-12 better build guide
2026-03-13 add direct index input
2026-03-17 display multisig address correctly
2026-03-19 implement alternating text rendering
2026-03-19 next beta
2026-03-20 initial cmake file
2026-03-20 remove eclipes project files
2026-03-23 better clangd support
2026-03-23 easier automation
2026-03-23 try to make it easier for agents to code here
2026-03-23 Cmake (#209)
    * initial cmake file
    * remove eclipes project files
    * better clangd support
    * easier automation
    * try to make it easier for agents to code here
2026-03-23 more info to agents
2026-03-25 add mnemonic verification function
2026-03-25 correct leftover in readme
2026-03-25 remove unnecessary defines
2026-03-25 remove excessive #ifdef
2026-03-25 tidier clangd integration
2026-03-25 more cleaning
2026-03-26 use ARM GCC Toolchain 15.2.rel1 and automate download
2026-03-26 re-add missing instructions
2026-03-26 add build workflow
2026-03-26 remove uv cache
2026-03-26 add pscslite to builder
2026-03-26 do not expect objcopy to be in PATH
2026-03-26 remove horizontal seps
2026-03-26 minor corrections
2026-04-01 increase max segment count to 128
2026-04-14 add devboard v2 hardware design files
    Add the full devboard v2 manufacturing and design package so the latest board revision artifacts are versioned with the project.
2026-04-27 add calldata hash (ERC-8213)
2026-05-04 add len check to mutually authenticate
2026-05-11 hash everywhere
2026-05-11 update changelog
2026-06-15 Add MSDS report
2026-06-18 support scV2
2026-06-18 add scv2 whitelist
2026-06-19 update compilation instructions
2026-06-29 make sign algo a param
2026-06-29 support INIT over SecureChannel V2
